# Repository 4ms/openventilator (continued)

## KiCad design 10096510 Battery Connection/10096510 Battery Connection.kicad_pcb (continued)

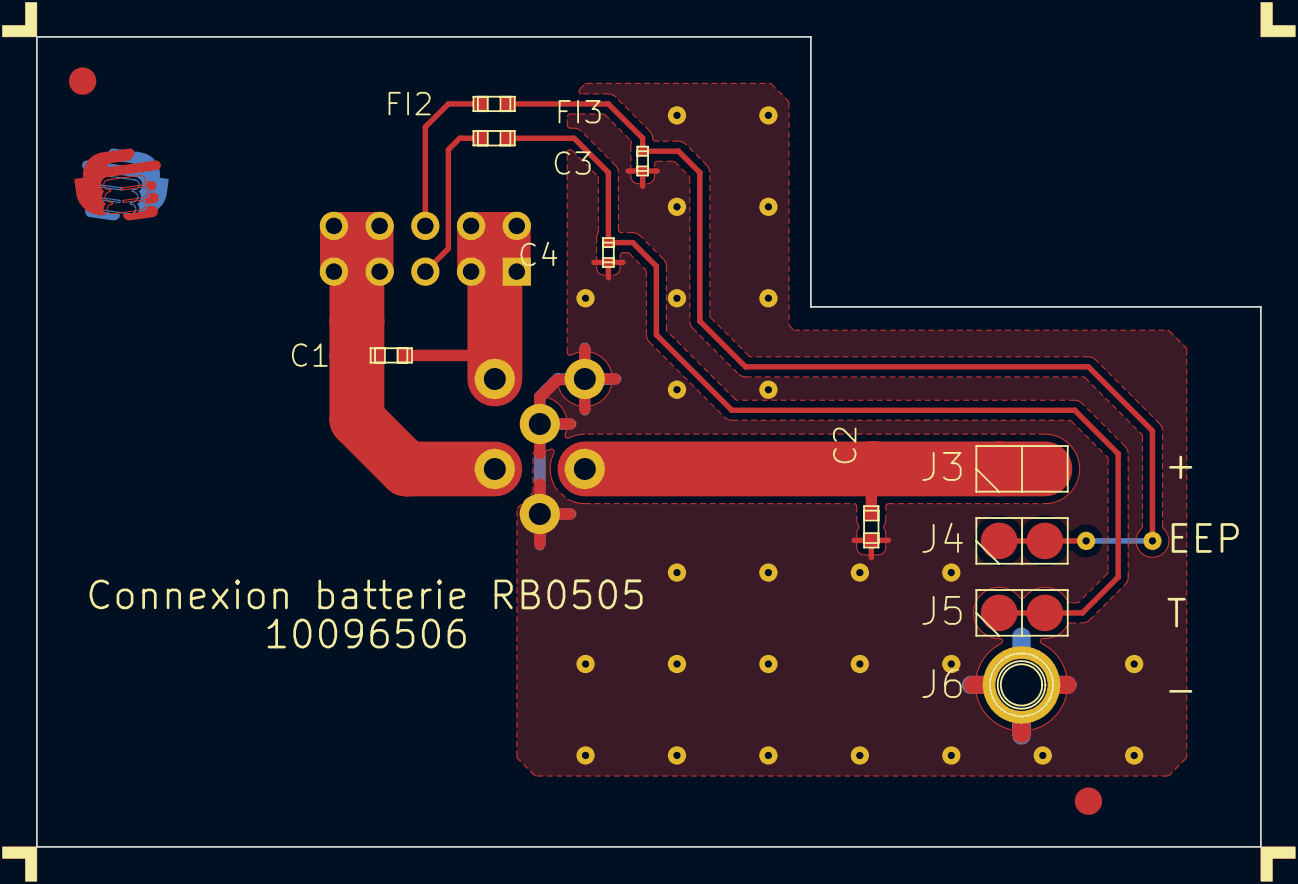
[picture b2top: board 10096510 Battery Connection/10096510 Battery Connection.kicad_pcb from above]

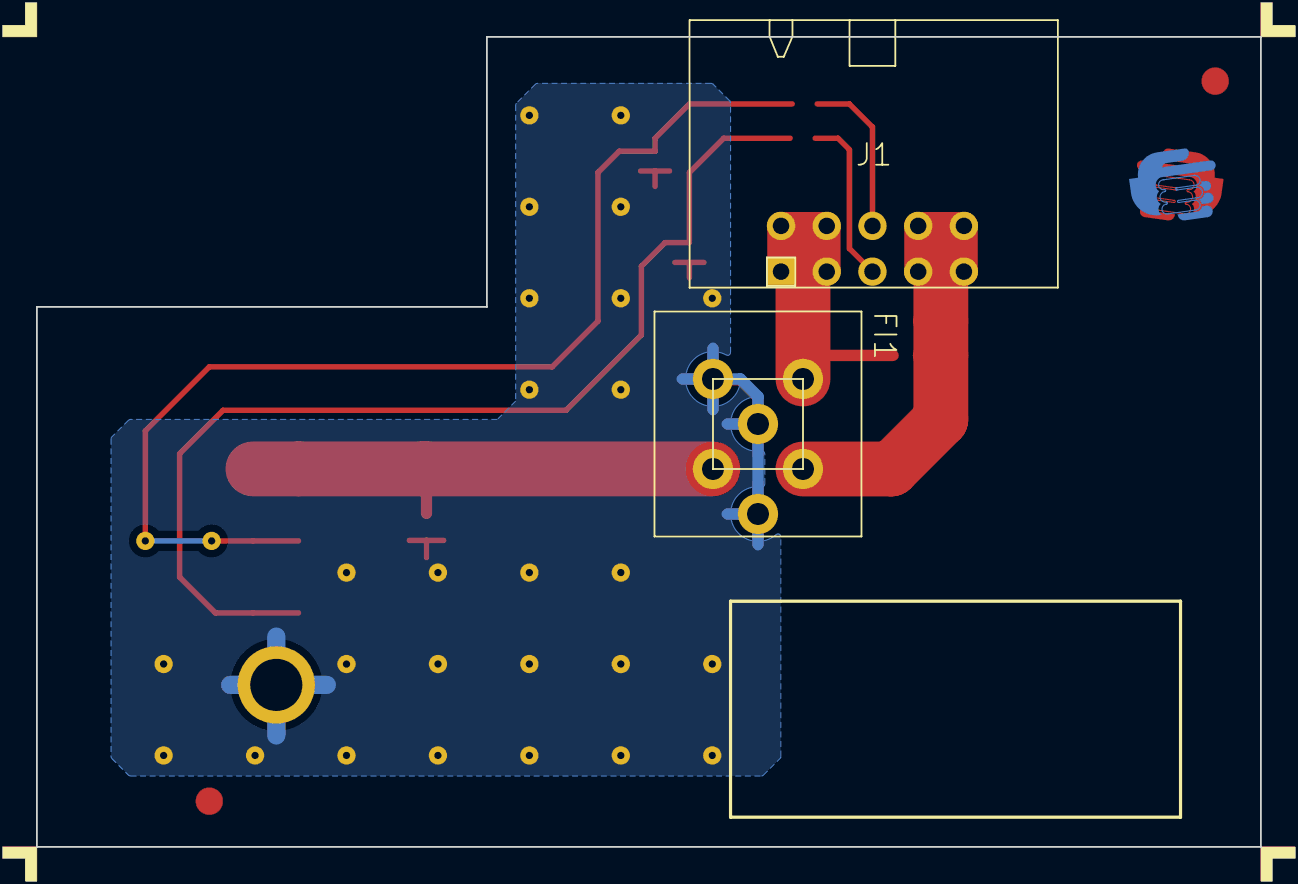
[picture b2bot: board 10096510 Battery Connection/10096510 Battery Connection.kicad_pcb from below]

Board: 2 copper layers, 68.0 x 45.0 mm, 55 parts (4 on the bottom side), 8 nets.

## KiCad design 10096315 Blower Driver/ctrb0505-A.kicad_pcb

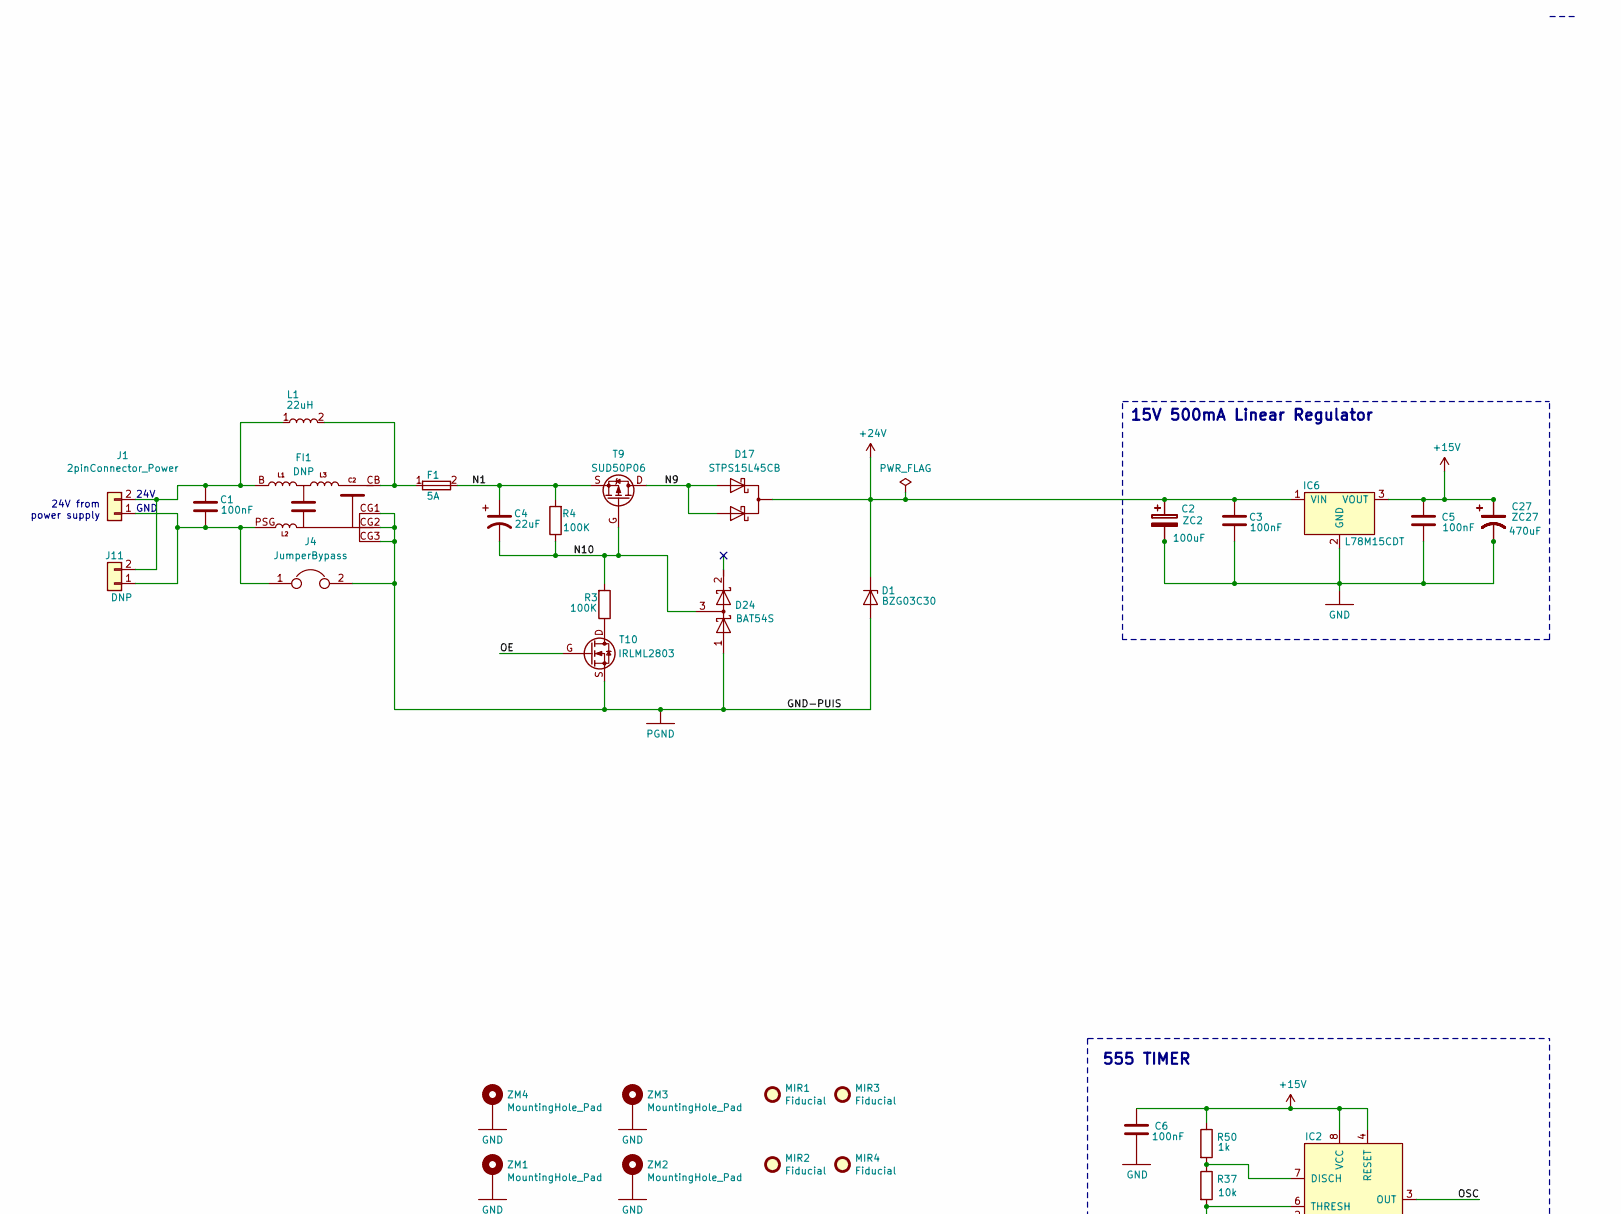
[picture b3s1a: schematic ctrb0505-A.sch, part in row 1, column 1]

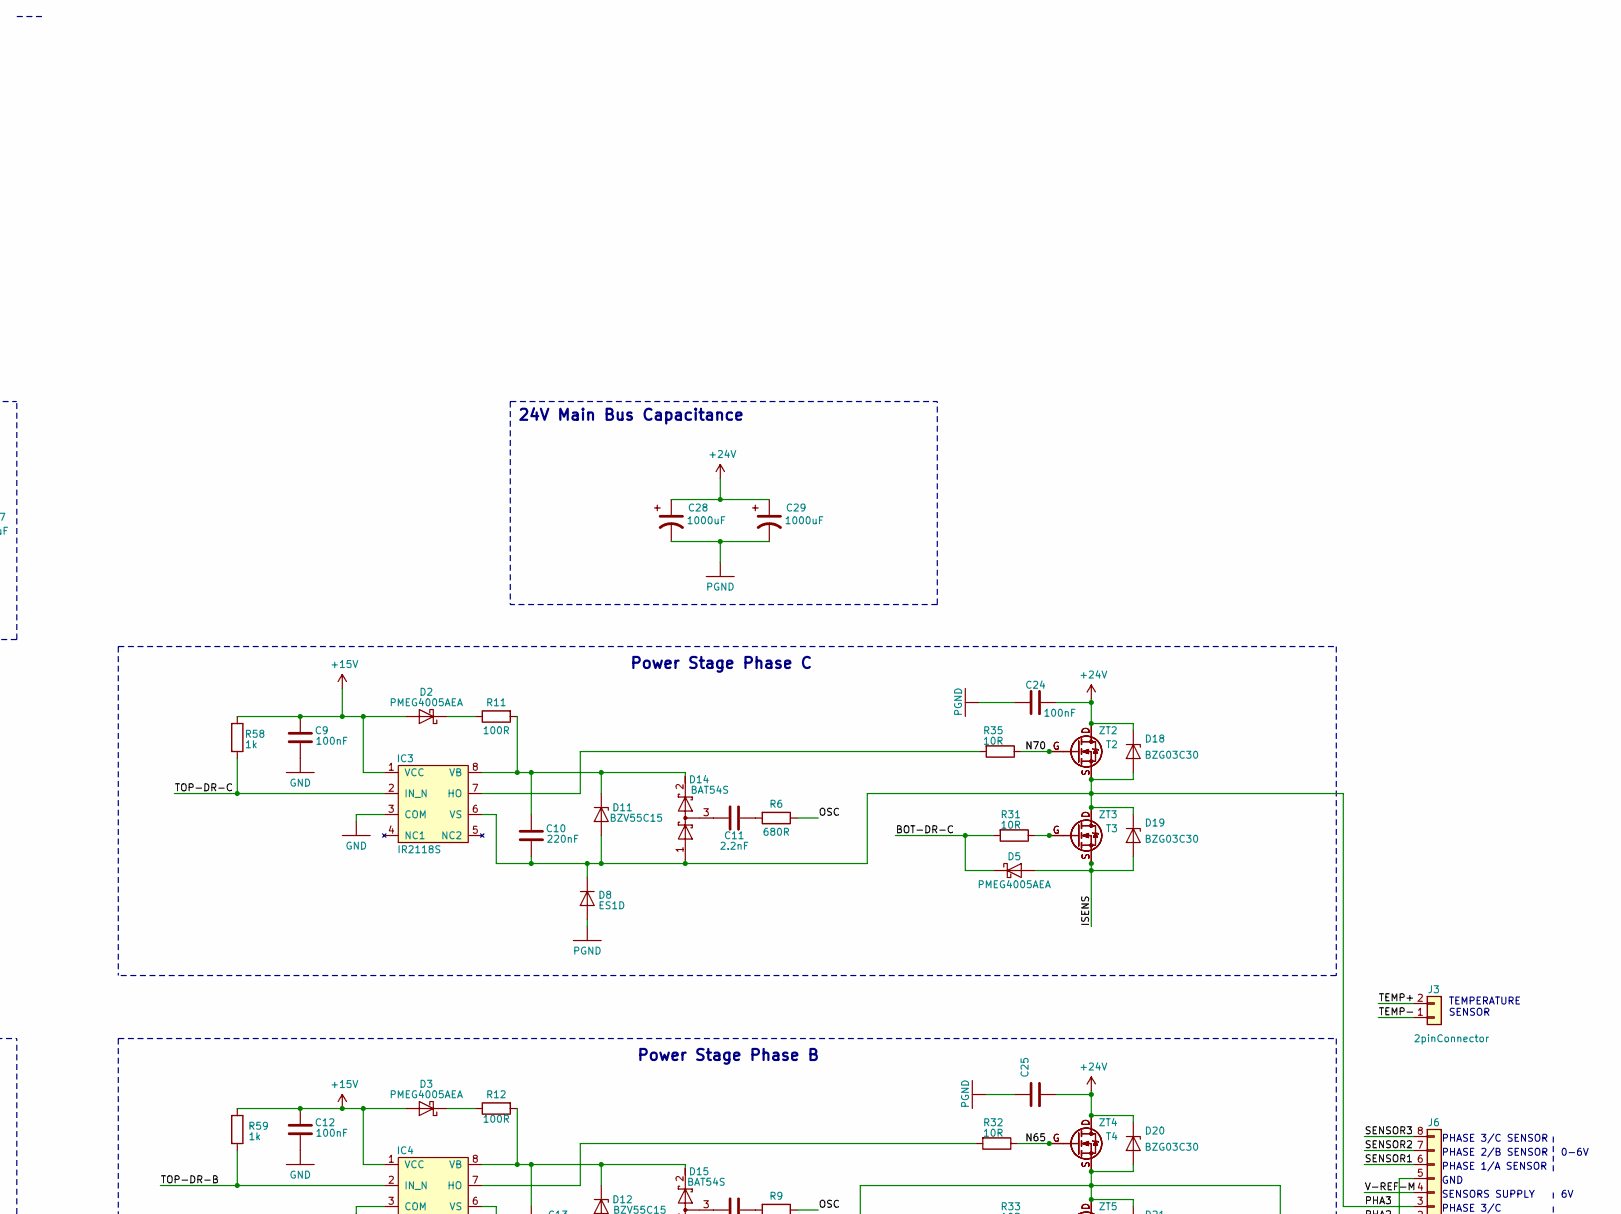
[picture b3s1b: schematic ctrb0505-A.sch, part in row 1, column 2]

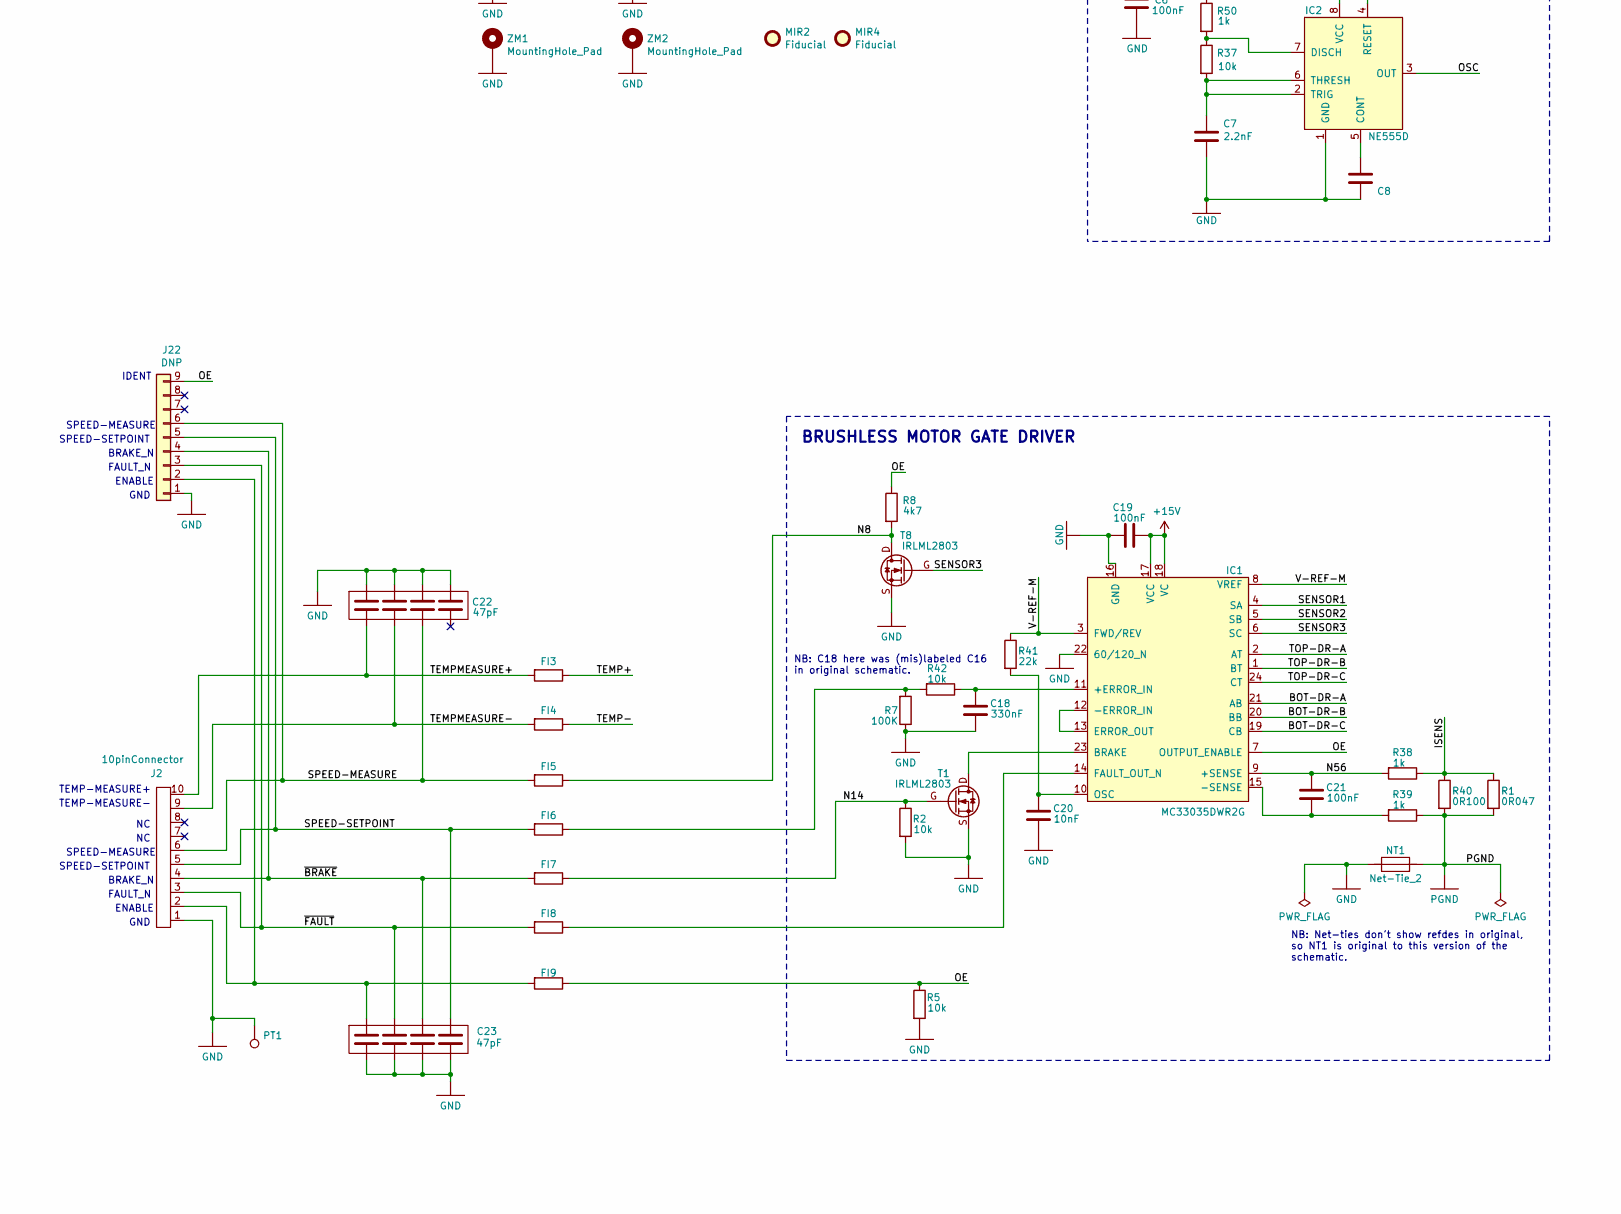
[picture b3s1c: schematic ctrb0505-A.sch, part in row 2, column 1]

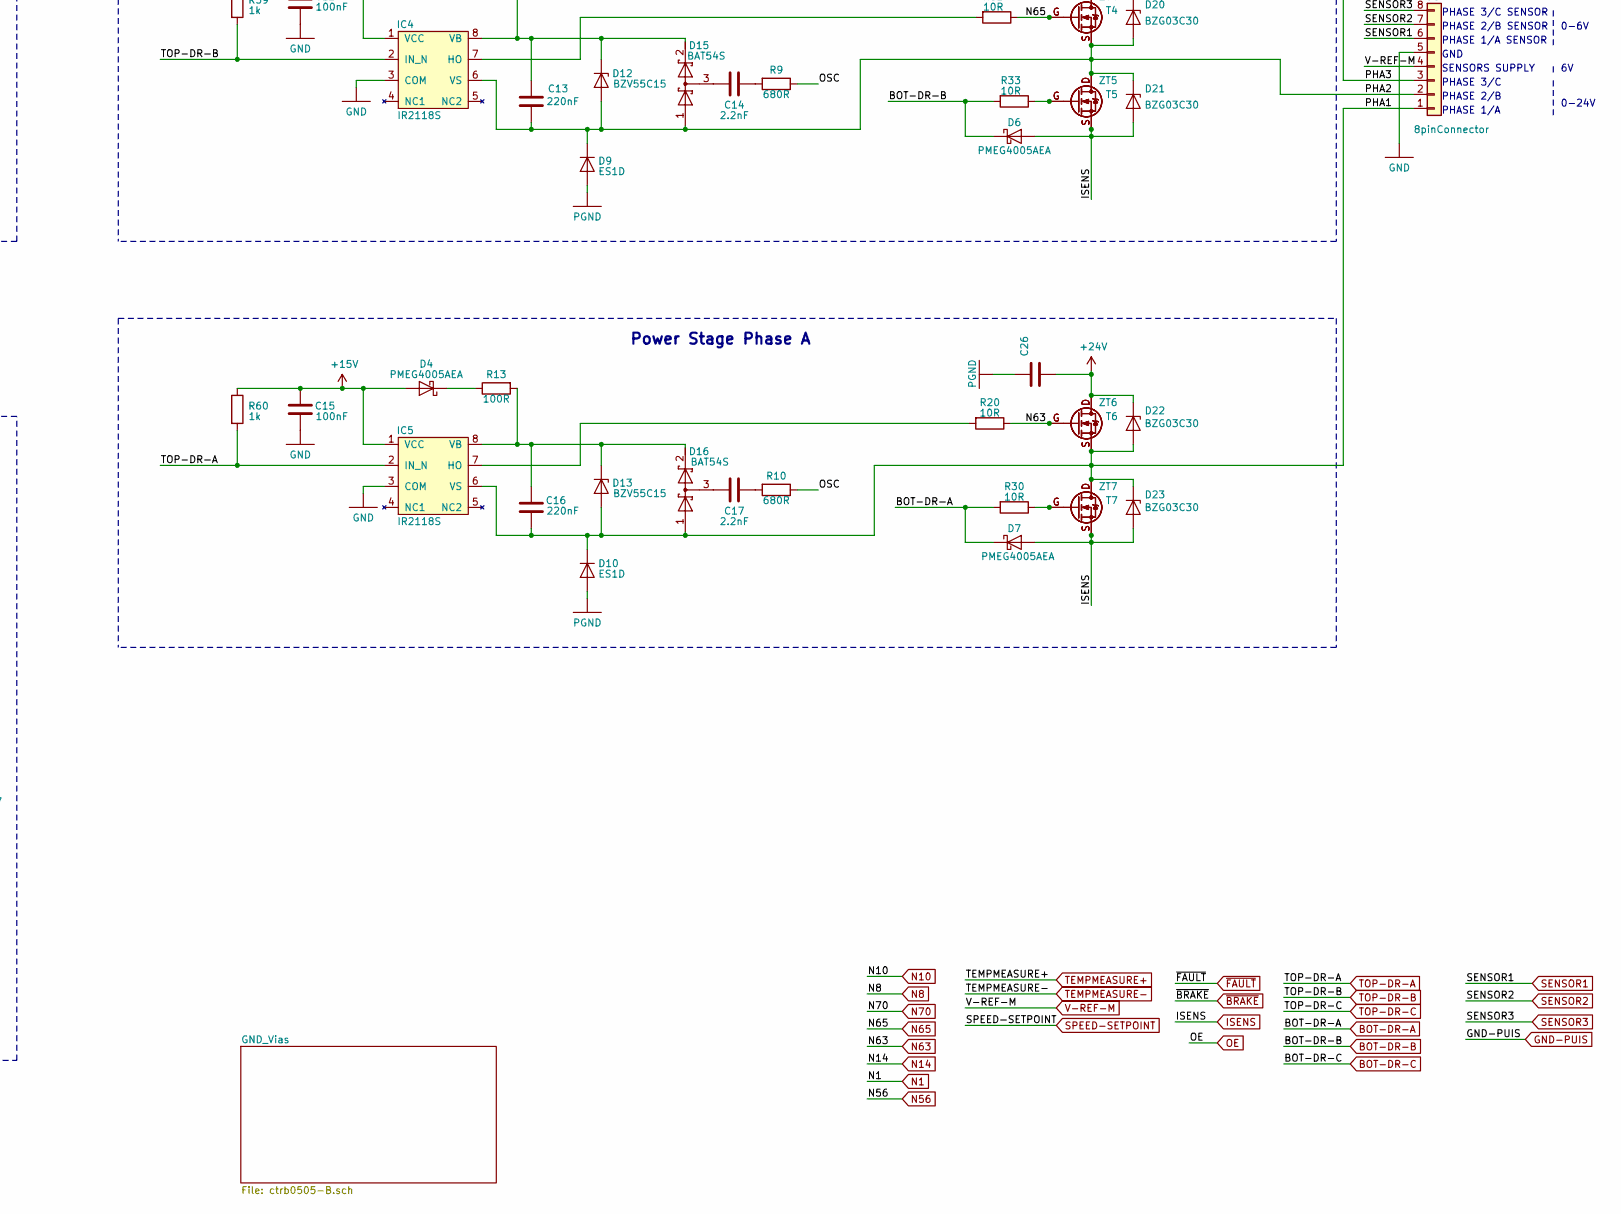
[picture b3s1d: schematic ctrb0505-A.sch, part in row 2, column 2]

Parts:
C1, C3, C5, C6, C9, C12, C15, C19, C21, C24, C25, C26: 100nF; C0805
C2: 100uF; 03515_10111101
C4: 22uF; C7343
C7, C11, C14, C17: 2.2nF; C0603
C8, C20: 10nF; C0603
C10, C13, C16: 220nF; RC1206
C18: 330nF; C0805
C22, C23: 47pF; C0612-4
C27: DNP; 03515_10111101
C28: 1000uF; HT-13X27_10111011
C29: 1000uF; HT-13X27_10011011
D1, D18, D19, D20, D21, D22, D23: BZG03C30; SMB
D2, D3, D4, D5, D6, D7: PMEG4005AEA; SOD323
D8, D9, D10: ES1D; SMA
D11, D12, D13: BZV55C15; SOD80
D14, D15, D16, D24: BAT54S; SOT23-1G
D17: STPS15L45CB; DPAK-2ANODES
F1: 5A; FU154000
FI1: DNP; BNX002_101110011011101110111011
FI3, FI4, FI5, FI6, FI7, FI8, FI9: FerriteBead; C0603
IC1: MotorDriver; MX.A24_COMPOSANT
IC2: NE555D; MX.A8_COMPOSANT
IC3, IC4, IC5: IR2118S; MX.A8_COMPOSANT
IC6: LinearRegulator; DPAK
J1: 2pinConnector_Power; MOL43650-02C
J2: 10pinConnector; BP2X5D_1101100110111011101110011001100110111011
J3: 2pinConnector; MOL7395-2_10011001
J4: JumperBypass; JUMPER2_NoCopper
J6: 8pinConnector; MOL7395-8_10111011101110111101101110111011
J11: DNP; MOL5566-2_10111011
J22: DNP; MOL7395-9_110110011001100110011001100110011011
L1: 22uH; ELC09DxxxxF_NoCopper
MIR1, MIR2, MIR3, MIR4: Fiducial; MIRECMS-SAFT
NT1: Net-Tie_2; NetTie-2_SMD_Pad_2.5x5mm
PT1: TestPoint; C12000
R1: 0R047; R2512
R2, R5, R37, R42: 10k; R0603
R3, R4, R7: 100K; R0603
R6, R9, R10: 680R; R0603
R8: 4k7; R0603
R11, R12, R13: 100R; R0603
R20, R30, R31, R32, R33, R35: 10R; R0603
R38, R39, R50: 1k; R0603
R40: 0R100; R2512
R41: 22k; R0603
R58, R59, R60: 1k; RC1206
T1, T8, T10: IRLML2803; SOT23-GSD
T2, T3, T4, T5, T6, T7: MOSFET_NMOS_55V; DPAK-GDS
T9: SUD50P06; DPAK-GDS
ZC2: 100uF; C-SC8
ZC27: 470uF; C-SC10
ZM1, ZM2, ZM3, ZM4: MountingHole_Pad; FIX35M_1101
ZT2, ZT4, ZT6: DNP; TO220ABGDS-INV_COUCHE_101110011001
ZT3, ZT5, ZT7: DNP; TO220ABGDS-INV_COUCHE_101110011011

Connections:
+15V: C5.2, C6.2, C9.2, C12.2, C15.2, C19.1, C27.+, D2.A, D3.A, D4.A, IC1.17 (VCC), IC1.18 (VC), IC2.4 (RESET), IC2.8 (VCC), IC3.1 (VCC), IC4.1 (VCC), IC5.1 (VCC), IC6.3 (VOUT), R50.2, R58.2, R59.2, R60.2, ZC27.+; also elsewhere on the board
+24V: C2.+, C3.2, C24.1, C25.1, C26.1, C28.+, C29.+, D1.K, D17.K, D18.K, D20.K, D22.K, IC6.1 (VIN), T2.D, T4.D, T6.D, ZC2.+, ZT2.D, ZT4.D, ZT6.D; also elsewhere on the board
/N9: D17.A1, D17.A2, T9.D
/OSC: IC2.3 (OUT), R6.2, R9.2, R10.2
/PHA1: C16.1, D10.K, D13.A, D16.1, D22.A, D23.K, IC5.6 (VS), J6.1, T6.S, T7.D, ZT6.S, ZT7.D
/PHA2: C13.1, D9.K, D12.A, D15.1, D20.A, D21.K, IC4.6 (VS), J6.2, T4.S, T5.D, ZT4.S, ZT5.D
/PHA3: C10.1, D8.K, D11.A, D14.1, D18.A, D19.K, IC3.6 (VS), J6.3, T2.S, T3.D, ZT2.S, ZT3.D
/SPEED-MEASURE: C22.3, FI5.1, J2.6, J22.6
/TEMP+: FI3.2, J3.2
/TEMP-: FI4.2, J3.1
BOT-DR-A: D7.K, IC1.21 (AB), R30.1; also elsewhere on the board
BOT-DR-B: D6.K, IC1.20 (BB), R33.1; also elsewhere on the board
BOT-DR-C: D5.K, IC1.19 (CB), R31.1; also elsewhere on the board
GND: C2.-, C3.1, C5.1, C6.1, C7.1, C8.1, C9.1, C12.1, C15.1, C18.2, C19.2, C20.1, C22.5, C22.6, C22.7, C22.8, C23.1, C23.2, C23.3, C23.4, C27.-, IC1.16 (GND), IC1.22 (60/120_N), IC2.1 (GND), IC3.3 (COM), IC4.3 (COM), IC5.3 (COM), IC6.2 (GND), J2.1, J6.5, J22.1, NT1.2, PT1.1, R2.1, R5.1, R7.1, T1.S, T8.S, ZC2.-, ZC27.-, ZM1.1, ZM2.1, ZM3.1, ZM4.1; also elsewhere on the board
GND-PUIS: C24.2, C25.2, C26.2, C28.-, C29.-, D1.A, D8.A, D9.A, D10.A, D24.1, FI1.CG1 (e), FI1.CG2, FI1.CG3, J4.2, NT1.1, R1.2, R39.2, R40.1, T10.S; also elsewhere on the board
ISENS: D5.A, D6.A, D7.A, D19.A, D21.A, D23.A, R1.1, R38.2, R40.2, T3.S, T5.S, T7.S, ZT3.S, ZT5.S, ZT7.S; also elsewhere on the board
N1: C4.+, F1.2, R4.2, T9.S; also elsewhere on the board
N8: FI5.2, R8.2, T8.D; also elsewhere on the board
N10: C4.-, D24.3, R3.2, R4.1, T9.G; also elsewhere on the board
N14: FI7.2, R2.2, T1.G; also elsewhere on the board
N56: C21.2, IC1.9 (+SENSE), R38.1; also elsewhere on the board
N63: R20.2, T6.G, ZT6.G; also elsewhere on the board
N65: R32.2, T4.G, ZT4.G; also elsewhere on the board
N70: R35.2, T2.G, ZT2.G; also elsewhere on the board
unnamed: C1.1, FI1.PSG, J1.1, J4.1, J11.1
unnamed: C1.2, FI1.B, J1.2, J11.2, L1.1
unnamed: C7.2, IC2.2 (TRIG), IC2.6 (THRESH), R37.1
unnamed: C8.2, IC2.5 (CONT)
unnamed: C10.2, D11.K, D14.2, IC3.8 (VB), R11.2
unnamed: C11.1, R6.1
unnamed: C11.2, D14.3
unnamed: C13.2, D12.K, D15.2, IC4.8 (VB), R12.2
unnamed: C14.1, R9.1
unnamed: C14.2, D15.3
unnamed: C16.2, D13.K, D16.2, IC5.8 (VB), R13.2
unnamed: C17.1, R10.1
unnamed: C17.2, D16.3
unnamed: C18.1, IC1.11 (+ERROR_IN), R42.2
unnamed: C20.2, IC1.10 (OSC), R41.2
unnamed: C21.1, IC1.15 (-SENSE), R39.1
unnamed: C23.8, FI9.1, J2.2, J22.2
unnamed: D2.K, R11.1
unnamed: D3.K, R12.1
unnamed: D4.K, R13.1
unnamed: F1.1, FI1.CB, L1.2
unnamed: FI6.2, R7.2, R42.1
unnamed: FI8.2, IC1.14 (FAULT_OUT_N)
unnamed: IC1.12 (-ERROR_IN), IC1.13 (ERROR_OUT)
unnamed: IC1.23 (BRAKE), T1.D
unnamed: IC2.7 (DISCH), R37.2, R50.1
unnamed: IC3.7 (HO), R35.1
unnamed: IC4.7 (HO), R32.1
unnamed: IC5.7 (HO), R20.1
unnamed: R3.1, T10.D
unnamed: R30.2, T7.G, ZT7.G
unnamed: R31.2, T3.G, ZT3.G
unnamed: R33.2, T5.G, ZT5.G
OE: FI9.2, IC1.7 (OUTPUT_ENABLE), J22.9, R5.2, R8.1, T10.G; also elsewhere on the board
SENSOR1: IC1.4 (SA), J6.6; also elsewhere on the board
SENSOR2: IC1.5 (SB), J6.7; also elsewhere on the board
SENSOR3: IC1.6 (SC), J6.8, T8.G; also elsewhere on the board
SPEED-SETPOINT: C23.5, FI6.1, J2.5, J22.5; also elsewhere on the board
TEMPMEASURE+: C22.1, FI3.1, J2.10; also elsewhere on the board
TEMPMEASURE-: C22.2, FI4.1, J2.9; also elsewhere on the board
TOP-DR-A: IC1.2 (AT), IC5.2 (IN_N), R60.1; also elsewhere on the board
TOP-DR-B: IC1.1 (BT), IC4.2 (IN_N), R59.1; also elsewhere on the board
TOP-DR-C: IC1.24 (CT), IC3.2 (IN_N), R58.1; also elsewhere on the board
V-REF-M: IC1.3 (FWD/REV), IC1.8 (VREF), J6.4, R41.1; also elsewhere on the board
~BRAKE~: C23.6, FI7.1, J2.4, J22.4; also elsewhere on the board
~FAULT~: C23.7, FI8.1, J2.3, J22.3; also elsewhere on the board

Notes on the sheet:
15V 500mA Linear Regulator
Power Stage Phase C
Power Stage Phase B
Power Stage Phase A
TEMPERATURE SENSOR
PHASE 3/C SENSOR
PHASE 2/B SENSOR
PHASE 1/A SENSOR
GND
SENSORS SUPPLY
PHASE 3/C
PHASE 2/B
PHASE 1/A
TEMP-MEASURE+
TEMP-MEASURE-
SPEED-MEASURE
SPEED-SETPOINT
BRAKE_N
FAULT_N
ENABLE
IDENT
555 TIMER
BRUSHLESS MOTOR GATE DRIVER
24V Main Bus Capacitance
NB: Net-ties don't show refdes in original, so NT1 is original to this version of the schematic.
NB: C18 here was (mis)labeled C16 in original schematic.
24V from power supply
24V
0-6V
0-24V

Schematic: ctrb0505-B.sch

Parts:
V1, V2, V4, V5, V6, V7, V8, V10, V11, V12, V13, V15, V16, V19, V20, V22, V23, V26, V27, V28, V29, V31, V32, V33, V35, V38, V39, V41, V42, V43, V47, V50, V52, V64, V66, V67, V68, V69, V70, V75, V76, V77, V78, V79, V80, V81, V82, V84: Via; VIA-091X03-VE_1011
V3, V44, V45, V65, V85, V86, V87: Via; VIA-091X03-VE_1001
V9, V14, V17, V18, V21, V24, V25, V30, V34, V36, V37, V40, V46, V48, V49, V51, V53, V54, V55, V56, V57, V58, V59, V60, V61, V62, V63, V71, V72, V73, V74, V83: Via; VIA-091X03-VE_1101

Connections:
+15V: V15.~, V16.~, V20.~, V33.~, V44.~, V75.~, V76.~; also elsewhere on the board
+24V: V45.~; also elsewhere on the board
BOT-DR-A: V41.~, V80.~; also elsewhere on the board
BOT-DR-B: V42.~, V79.~; also elsewhere on the board
BOT-DR-C: V43.~, V78.~; also elsewhere on the board
GND: V9.~, V14.~, V17.~, V18.~, V21.~, V24.~, V25.~, V30.~, V34.~, V36.~, V37.~, V40.~, V46.~, V48.~, V49.~, V51.~, V53.~, V54.~, V55.~, V56.~, V57.~, V58.~, V59.~, V60.~, V61.~, V62.~, V63.~, V71.~, V72.~, V73.~, V74.~, V83.~; also elsewhere on the board
GND-PUIS: V7.~, V8.~, V10.~, V32.~, V38.~; also elsewhere on the board
ISENS: V4.~, V5.~, V6.~; also elsewhere on the board
N1: V65.~; also elsewhere on the board
N8: V29.~, V64.~; also elsewhere on the board
N10: V1.~, V2.~, V3.~; also elsewhere on the board
N14: V47.~, V77.~; also elsewhere on the board
N56: V35.~, V39.~; also elsewhere on the board
N63: V87.~; also elsewhere on the board
N65: V86.~; also elsewhere on the board
N70: V85.~; also elsewhere on the board
OE: V31.~; also elsewhere on the board
SENSOR1: V27.~; also elsewhere on the board
SENSOR2: V28.~; also elsewhere on the board
SENSOR3: V82.~; also elsewhere on the board
SPEED-SETPOINT: V68.~, V69.~; also elsewhere on the board
TEMPMEASURE+: V52.~; also elsewhere on the board
TEMPMEASURE-: V70.~; also elsewhere on the board
TOP-DR-A: V13.~, V23.~; also elsewhere on the board
TOP-DR-B: V12.~, V22.~; also elsewhere on the board
TOP-DR-C: V11.~, V19.~; also elsewhere on the board
V-REF-M: V26.~, V81.~; also elsewhere on the board
~BRAKE~: V67.~, V84.~; also elsewhere on the board
~FAULT~: V50.~, V66.~; also elsewhere on the board

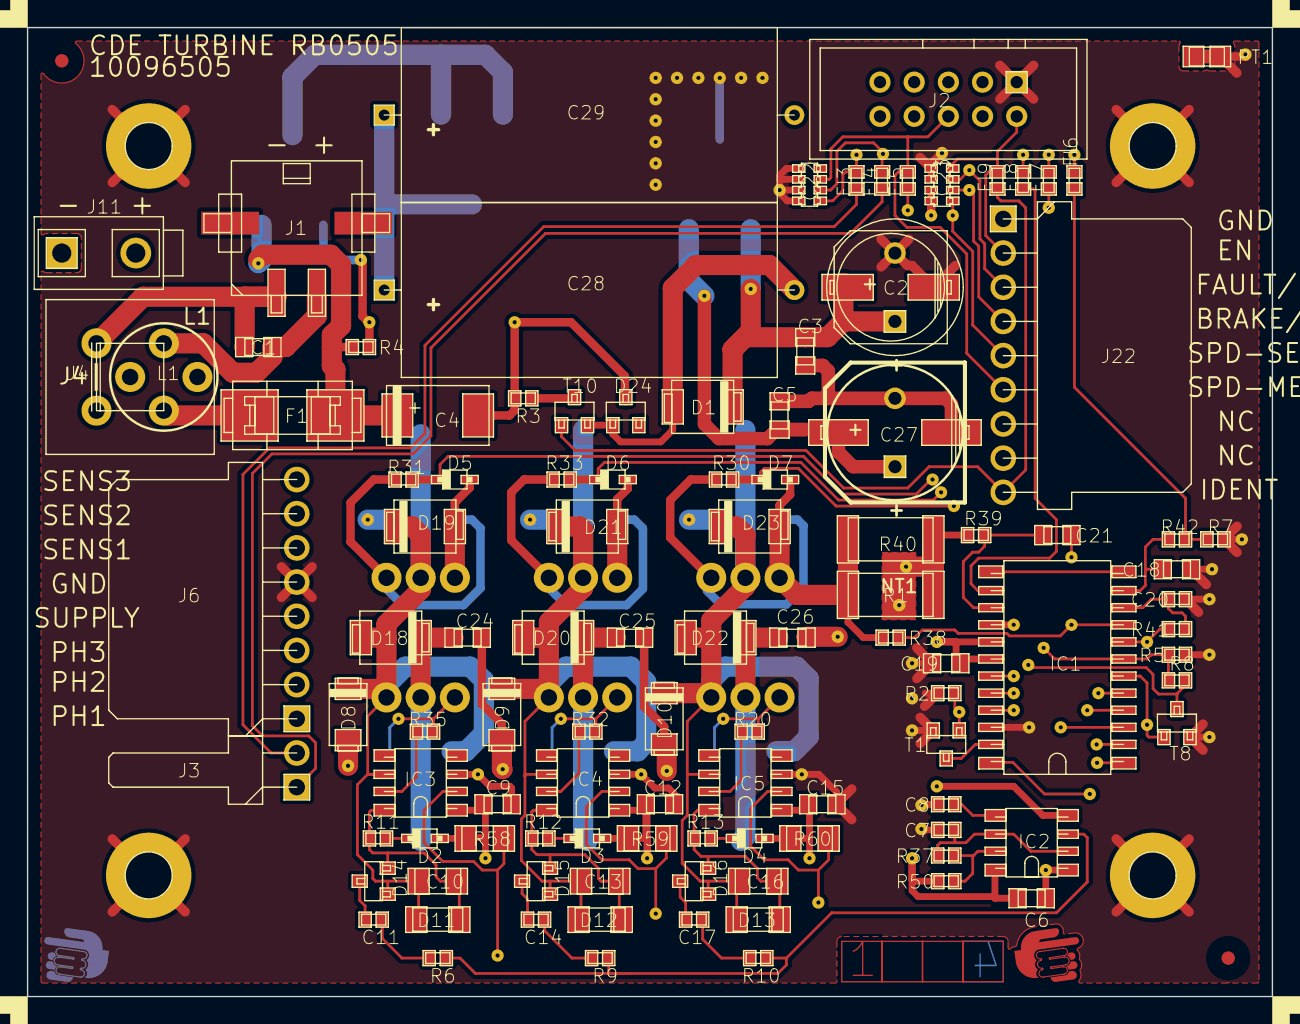
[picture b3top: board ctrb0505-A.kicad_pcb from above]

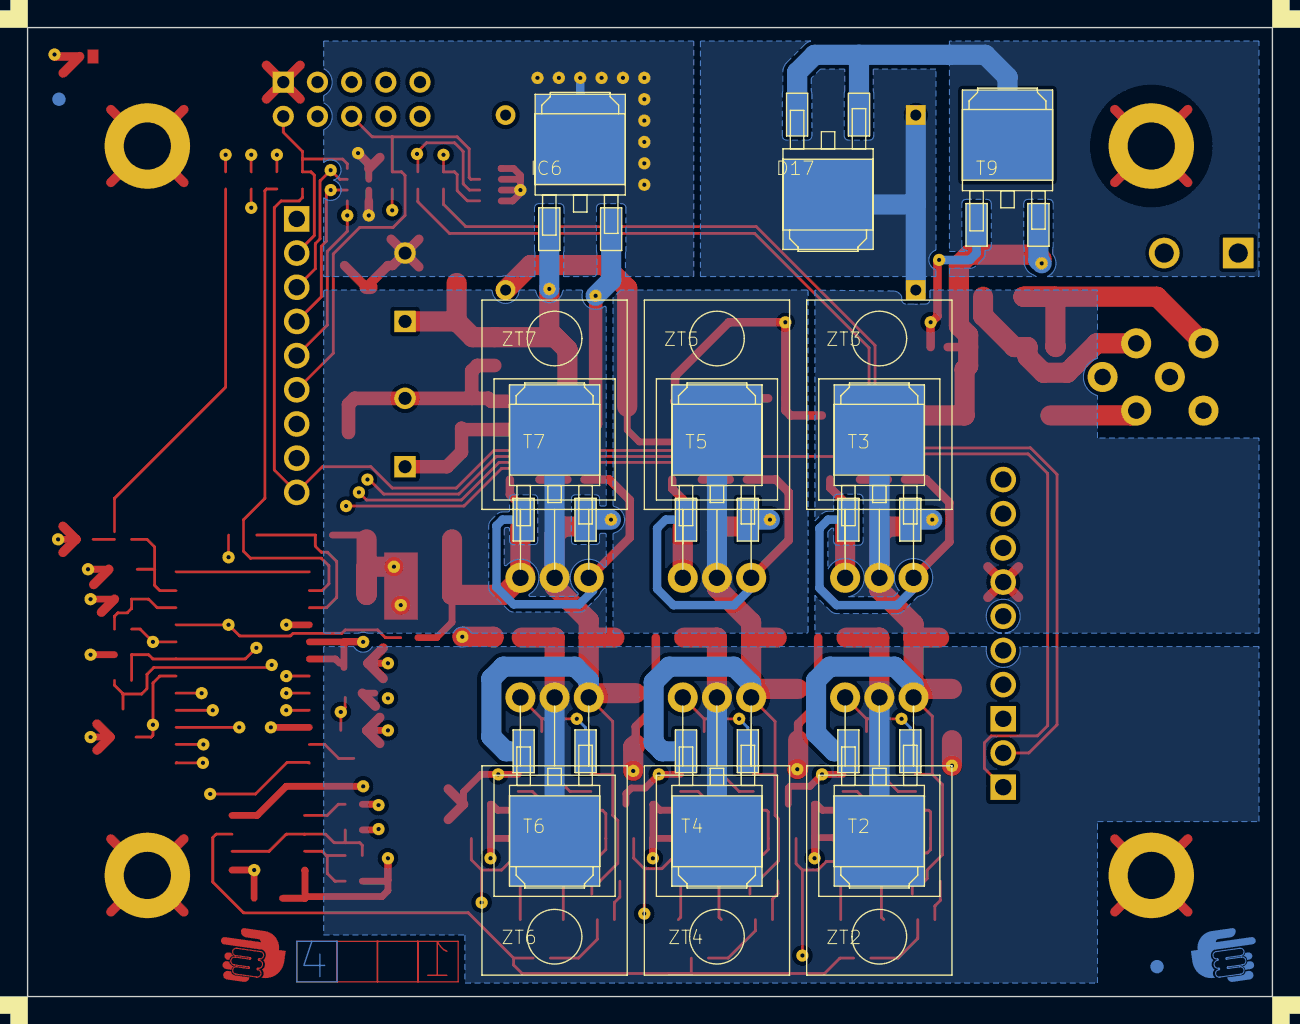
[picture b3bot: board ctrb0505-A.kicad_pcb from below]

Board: 4 copper layers, 92.5 x 72.0 mm, 233 parts (19 on the bottom side), 70 nets.

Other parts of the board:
cam1, cam2, cam3, cam4: COIN_EXTERNE
cam5: FILM18_HORIZONTAL
cam6: A3_PER_COVIDIEN
cam7: A3_EQFC_COVIDIEN
cam8: PER-COVIDIEN_TEXTE
cam9: A3_EQFS_COVIDIEN
cam12: FABRICATION-FEE; FABRICATION-FEE_0.6666
cam13: PERCAGE_TABLEAU; PERCAGE_TABLEAU_0.666
cam14, cam15: FEE_COMP; FEE_COMP_0.3

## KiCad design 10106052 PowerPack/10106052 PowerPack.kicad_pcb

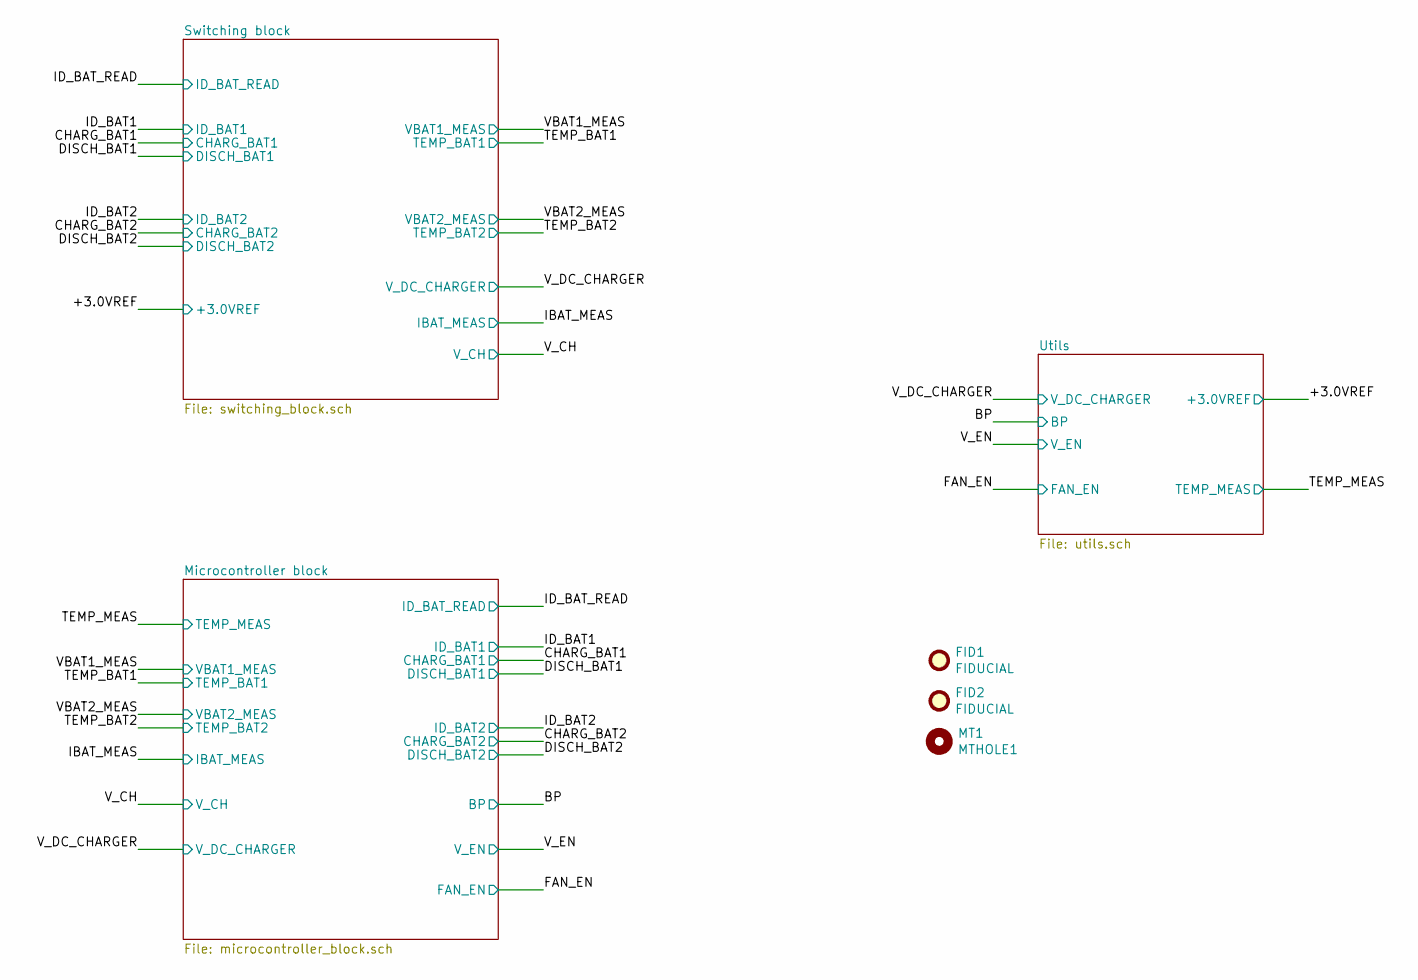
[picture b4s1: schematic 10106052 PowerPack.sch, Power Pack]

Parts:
FID1, FID2: FIDUCIAL
MT1: MTHOLE1
